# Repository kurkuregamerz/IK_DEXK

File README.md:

# IK DEXK 
IK DEXK is a macropad that has 16 MX Keyboard switches and 1 OLED 0.91 inch Display.

## Preview of Designs  

## Features
*  It includes an 0.91 inch OLED display.
*  Custom Macros for efficiency.
*  Has high performance Cherry MX Switches with white keycaps.
*  Custom PCB and Case.

## THE PROCESS 
I at first designed the Macropad to be 3x3 but during designing I made some mistakes which later in firmware development caused a huge problem.
So when I ran into that problem I thought that now I know how things work so why not make it larger. That is why I made the macropad 4x4.
Here are some images of design which were used at first.

# BILL OF MATARIALS
* TOTAL IS $54.86 with delivery charge.<br/>

<table>
  <tr>
    <th>ITEM</th>
    <th>SOURCE</th>
    <th>PRICE</th>
    <th>DELIVERY CHARGE</th>
    <th>TOTAL</th>
  </tr>
  <tr>
    <td>PCB</td>
    <td>JLCPCB</td>
    <td>$ 4.00</td>
    <td>$ -</td>
    <td>$ 4.00</td>
  </tr>
  <tr>
    <td>CASE-BOTTOM</td>
    <td>JLC3DP</td>
    <td>$ 22.34</td>
    <td>$ 24.58</td>
    <td>$ 46.92</td>
  </tr>
   <tr>
    <td>CASE-TOP</td>
    <td>JLC3DP</td>
    <td>$ 3.94</td>
    <td>$ -</td>
    <td>$ 3.94</td>
  </tr>
  <tr>
    <td>HACKPAD KIT</td>
    <td>HACKCLUB</td>
    <td>$ -</td>
    <td>$ -</td>
    <td>$ 0.00</td>
  </tr>
  <tr>
    <td>TOTAL</td>
    <td></td>
    <td>$ 30.28</td>
    <td>$ 24.58</td>
    <td>$ 54.86</td>
  </tr>
</table>

# How to get the parts if you wanna build it

### Start with JLCPCB for the PCB.

1. Visit <a src="https://jlcpcb.com">jlcbcb.com</a>.
2. Click on <b>Get Instant Quote</b>.
3. Upload <b>IK_DEXK-PCB_GERBER.zip</b> present in the production folder.
4. Select a color of your choice and the quantity.
5. Add to cart.

### After the PCB we need to get the case.

1. Visit <a src="https://jlc3dp.com">jlcbcb.com</a>.
2. Click on <b>Get Instant Quote</b>.
3. Upload <b>CASE BOTTOM.step</b> and <b>CASE TOP.step</b> present in the production folder.
4. Select a color and matarial of your choice.
5. Add to cart.

Other Items direct buy link you will find in <a src="./BOM.csv">BOM.csv</a>.

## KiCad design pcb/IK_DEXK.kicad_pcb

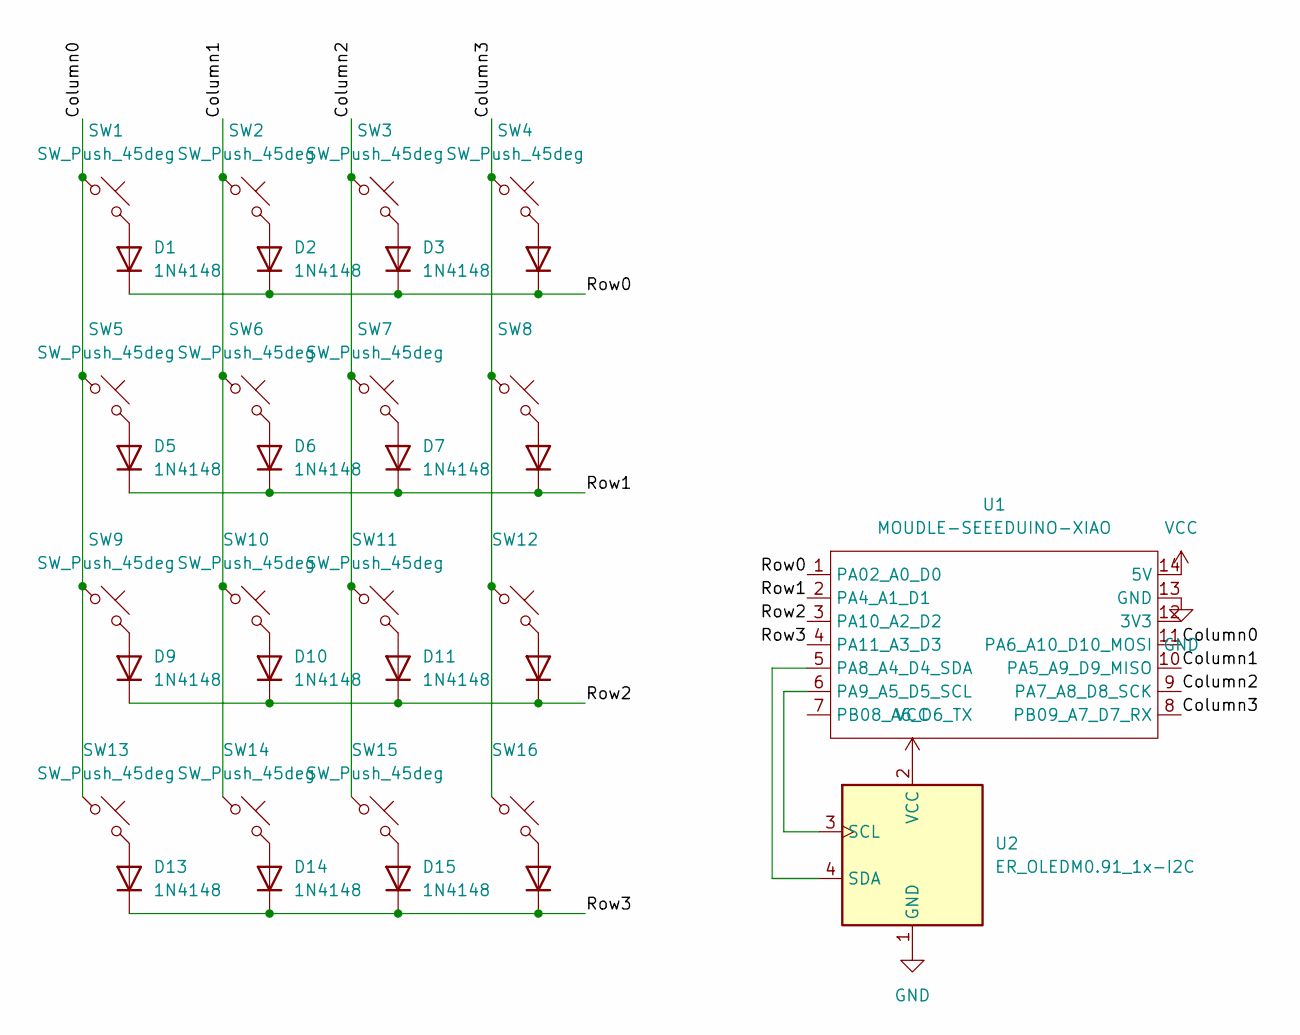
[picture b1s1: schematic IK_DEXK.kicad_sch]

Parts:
D1, D2, D3, D4, D5, D6, D7, D8, D9, D10, D11, D12, D13, D14, D15, D16: 1N4148; D_DO-35_SOD27_P7.62mm_Horizontal
SW1, SW2, SW3, SW4, SW5, SW6, SW7, SW8, SW9, SW10, SW11, SW12, SW13, SW14, SW15, SW16: SW_Push_45deg; SW_Cherry_MX_1.00u_PCB
U1: MOUDLE-SEEEDUINO-XIAO; XIAO-Generic-Hybrid-14P-2.54-21X17.8MM
U2: ER_OLEDM0.91_1x-I2C

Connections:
/Column0: SW1.1, SW5.1, SW9.1, SW13.1, U1.11 (PA6_A10_D10_MOSI)
/Column1: SW2.1, SW6.1, SW10.1, SW14.1, U1.10 (PA5_A9_D9_MISO)
/Column2: SW3.1, SW7.1, SW11.1, SW15.1, U1.9 (PA7_A8_D8_SCK)
/Column3: SW4.1, SW8.1, SW12.1, SW16.1, U1.8 (PB09_A7_D7_RX)
/Row0: D1.1 (K), D2.1 (K), D3.1 (K), D4.1 (K), U1.1 (PA02_A0_D0)
/Row1: D5.1 (K), D6.1 (K), D7.1 (K), D8.1 (K), U1.2 (PA4_A1_D1)
/Row2: D9.1 (K), D10.1 (K), D11.1 (K), D12.1 (K), U1.3 (PA10_A2_D2)
/Row3: D13.1 (K), D14.1 (K), D15.1 (K), D16.1 (K), U1.4 (PA11_A3_D3)
GND: U1.13 (GND), U2.1 (GND)
unnamed: D1.2 (A), SW1.2
unnamed: D2.2 (A), SW2.2
unnamed: D3.2 (A), SW3.2
unnamed: D4.2 (A), SW4.2
unnamed: D5.2 (A), SW5.2
unnamed: D6.2 (A), SW6.2
unnamed: D7.2 (A), SW7.2
unnamed: D8.2 (A), SW8.2
unnamed: D9.2 (A), SW9.2
unnamed: D10.2 (A), SW10.2
unnamed: D11.2 (A), SW11.2
unnamed: D12.2 (A), SW12.2
unnamed: D13.2 (A), SW13.2
unnamed: D14.2 (A), SW14.2
unnamed: D15.2 (A), SW15.2
unnamed: D16.2 (A), SW16.2
unnamed: U1.5 (PA8_A4_D4_SDA), U2.4 (SDA)
unnamed: U1.6 (PA9_A5_D5_SCL), U2.3 (SCL)
VCC: U1.14 (5V), U2.2 (VCC)

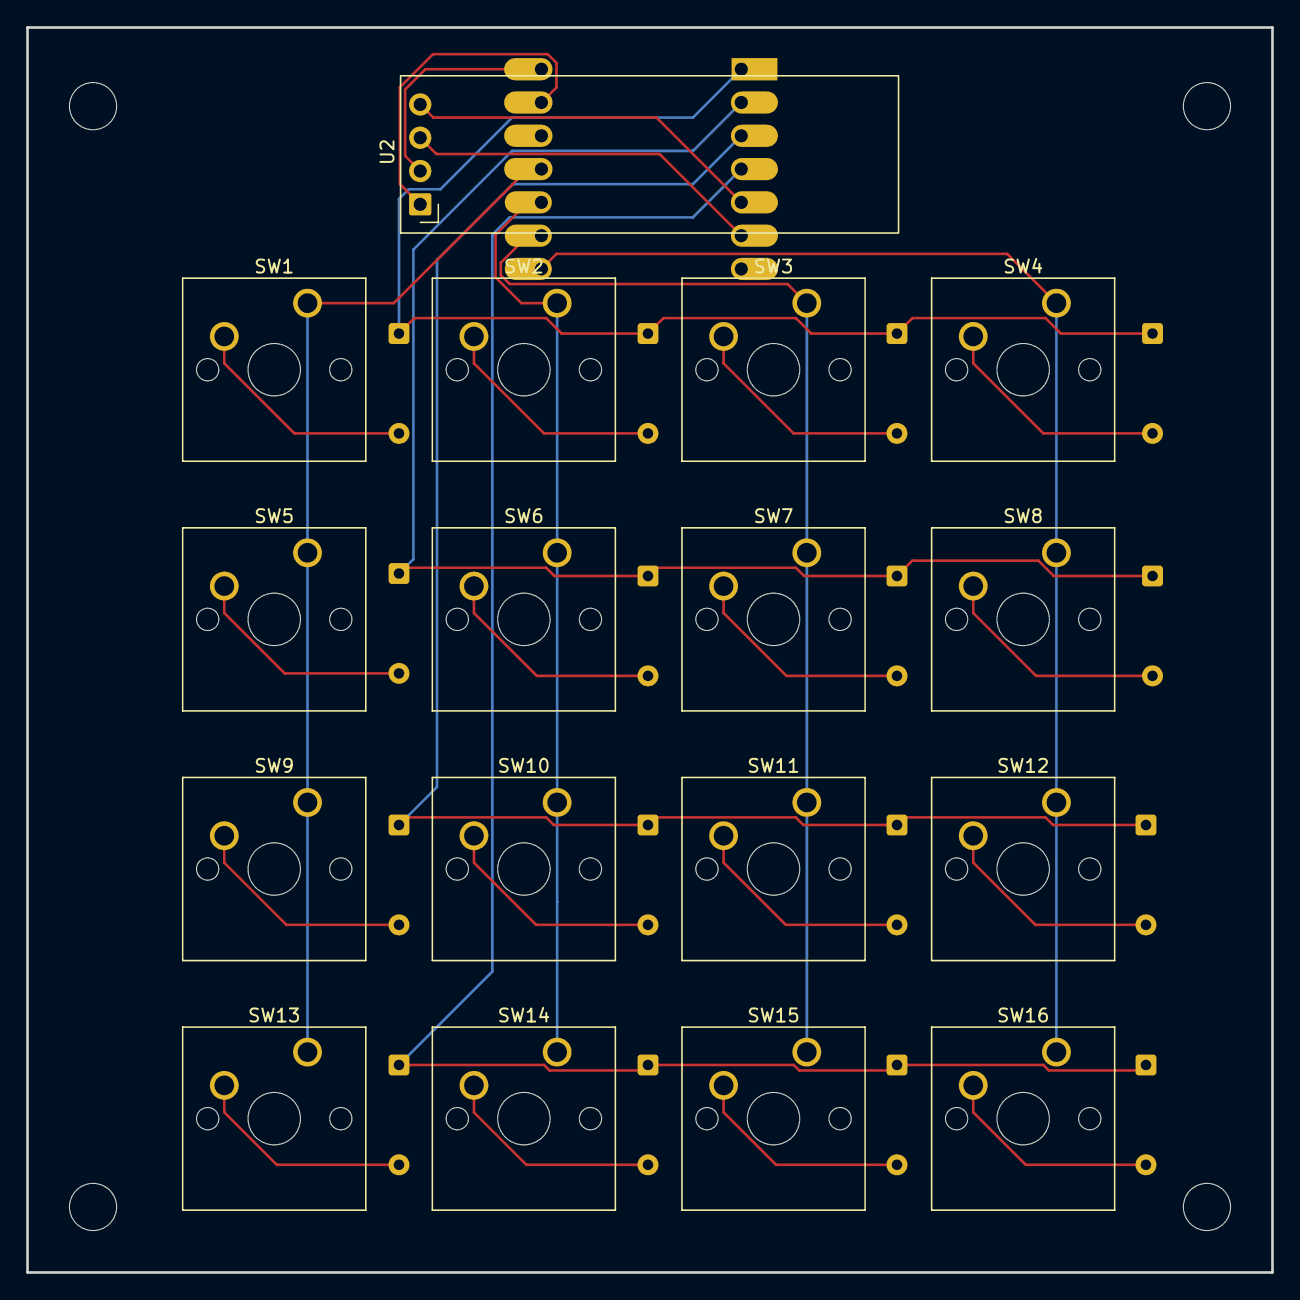
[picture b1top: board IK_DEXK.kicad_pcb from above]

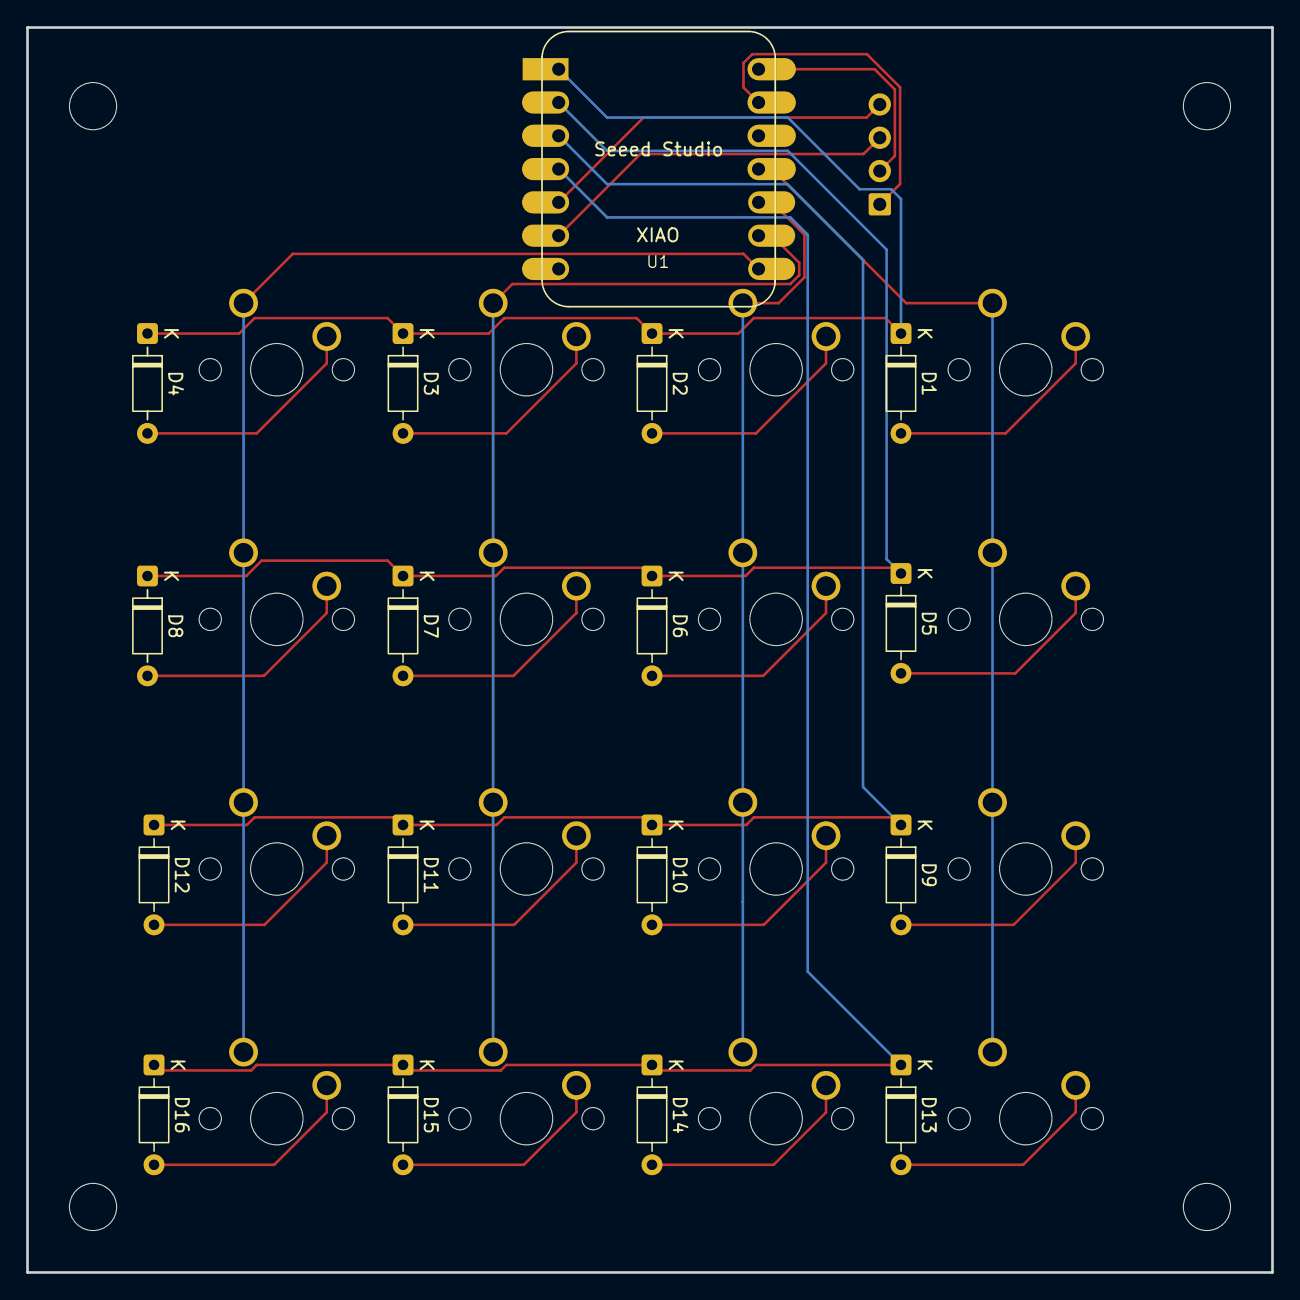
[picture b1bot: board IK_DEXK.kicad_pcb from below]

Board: 2 copper layers, 95.0 x 95.0 mm, 34 parts (17 on the bottom side), 28 nets.
